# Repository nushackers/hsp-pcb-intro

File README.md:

# Hackerspace: "Intro to PCB Design" workshop

This repository contains a basic USB-C LED PCB project using KiCad 9. KiCad is a
free/libre and open-source project (FLOSS), and you can download this electronic
design automation (EDA) software from
[their website](https://www.kicad.org/download/).

We assume that this PCB board will be manufactured by
[JLCPCB](https://jlcpcb.com/), so component sourcing is done through
[their parts catalogue](https://jlcpcb.com/parts/all-electronic-components), and
the PCB manufacturing capabilities are
[conformant to theirs](https://jlcpcb.com/capabilities/pcb-capabilities). We
will also use
[Bouni's KiCAD JLCPCB tools plugin](https://github.com/bouni/kicad-jlcpcb-tools)
to generate the final gerber files to send to JLCPCB for fabrication.

## Workshop resources

This PCB project is done as part of Hackerspace's "_Intro to PCB Design_"
workshop, held on Wednesday, 04 February 2026, from 1500h to 1700h (UTC+8). You
may access the accompanying [workshop slides](https://hckr.cc/hsp-pcb-intro),
and the [workshop recording](https://www.youtube.com/watch?v=2ei3KIMcw2c).

## License

This repository is licensed under [CERN-OHL-P-2.0](./LICENSE.md).

## Acknowledgements

The
[3D model for the TS-1187A-B-A-B button](./3dmodels/usb_led.3dshapes/TS-1187A-B-A-B.step)
is obtained from
[MaloufSleep's ME-ESP8266 open-source project](https://github.com/MaloufSleep/ME-ESP8266/blob/master/3D_Models/Button_Switch_SMD.3dShapes/TS-1187A-B-A-B.step).

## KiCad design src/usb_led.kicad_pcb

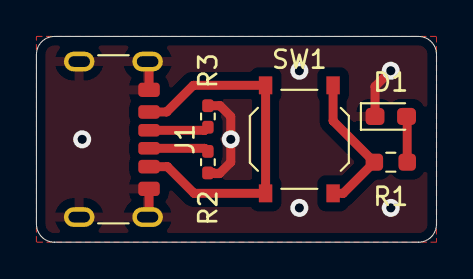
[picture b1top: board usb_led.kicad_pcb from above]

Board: 2 copper layers, 22.2 x 11.4 mm, 6 parts (0 on the bottom side), 6 nets.

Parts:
D1: LED_RED; LED_0603_1608Metric_Pad1.05x0.95mm_HandSolder
J1: HX TYPE-C 6PIN; USB_C_Receptacle_GCT_USB4125-xx-x_6P_TopMnt_Horizontal
R1: 150R; R_0603_1608Metric_Pad0.98x0.95mm_HandSolder
R2, R3: 5k1; R_0402_1005Metric_Pad0.72x0.64mm_HandSolder
SW1: BTN_ON; SW_Push_1P1T_XKB_TS-1187A

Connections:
GND: D1.1 (K), J1.A12 (GND), J1.B12 (GND), J1.S1 (SHIELD), R2.2, R3.2
unnamed: D1.2 (A), R1.2
unnamed: J1.A5 (CC1), R3.1
unnamed: J1.B5 (CC2), R2.1
unnamed: J1.A9 (VBUS), J1.B9 (VBUS), SW1.1
unnamed: R1.1, SW1.2

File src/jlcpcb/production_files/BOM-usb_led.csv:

Comment,Designator,Footprint,LCSC,Quantity
150R,R1,R_0603_1608Metric_Pad0.98x0.95mm_HandSolder,C22808,1
5k1,"R2,R3",R_0402_1005Metric_Pad0.72x0.64mm_HandSolder,C25905,2
BTN_ON,SW1,SW_Push_1P1T_XKB_TS-1187A,C318884,1
HX TYPE-C 6PIN,J1,USB_C_Receptacle_GCT_USB4125-xx-x_6P_TopMnt_Horizontal,C18357552,1
LED_RED,D1,LED_0603_1608Metric_Pad1.05x0.95mm_HandSolder,C2286,1

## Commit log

2026-02-04 chore: init
    Add KiCad hardware source files.
2026-02-04 docs: add JLCPCB plugin documentation
    Add usage of Bouni's KiCAD JLCPCB tools plugin to README file.
    Add PCB copper traces between important GND pads.
    Add final PCB 3D render image to README file.
2026-02-04 fix: regenerate JLCPCB gerber and production files
    Regenerate JLCPCB gerber files generated by the KiCad JLCPCB tools
    plugin.
    Update `.gitignore` to not exclude JLCPCB production files.
2026-02-04 docs: add workshop recording to README
    Add workshop recording YouTube link to README file.
    Update some minor wording in README file.
